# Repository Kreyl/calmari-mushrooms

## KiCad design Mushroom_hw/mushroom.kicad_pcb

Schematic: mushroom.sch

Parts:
ANT1: ANT_PCB_NOCNTR
B1, B2, B3: BAT
C1, C6, C12, C14, C19, C20, C23, C24, C26: 0.1u
C2, C8, C11, C13, C15, C16, C21, C28: 10u
C3: 10u; CAP_0603
C4, C5, C7, C29, C30, C31: 0.1u; CAP_0603
C9: 10n; CAP_0603
C10: 1u; CAP_0603
C17, C18: 10pF; CAP_0603
C22, C25, C27: 220pF
D1, D2, D3: SS14
DA1, DA3, DA4: TPS61042
DA2: NCP583SQ
DD1: STM32L151CXTX
DD2: CC2500
F1, F2, F3, F4, F5, F6, F7, F8, F9, F10, F11, F12, F13, F14, F15, F16, F17, F18, F19, F20: FUSE0R
HOLE1, HOLE2, HOLE3, HOLE4: HOLE_METALLED
L1, L2, L3: 6.8uH; IND_1210
Q1, Q3, Q6: LED_RGB_WS2812B
Q2, Q4, Q5: LED_RGB
R1, R2: 4K7; RES_0402
R3, R8, R15: 100k
R4: 150; RES_0402
R5, R11, R16: 10k; RES_0603
R6, R12, R17: 13R; RES_0603
R7, R13, R18: 120k; RES_0603
R9, R10: 390k; RES_0603
R14: 56k
R19, R20, R21: 51R; RES_0603
RP1, RP2: REFPOINT
SW1: SWITCH_H
TP1, TP2, TP3: TESTPOINT
XL1, XL5, XL6, XL8, XL9, XL10, XL12, XL13, XL14, XL16, XL17, XL18, XL20, XL21, XL22, XL24: CONN_3
XL2: ST_SWD
XL3: CONN_4
XL4: CONN_4
XL7, XL11, XL15, XL19, XL23: CONN_1
XTAL1: 27MHz; 03225

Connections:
+3.3V: C3.1, C4.1, C5.1, C7.1, C9.1, C10.1, C12.1, C13.1, C22.1, C23.1, C24.1, C25.1, C26.1, C27.1, DA2.3 (Vout), DD1.1, DD1.9, DD1.24, DD1.36, DD1.48, DD2.4 (DVDD), DD2.9 (AVDD), DD2.11 (AVDD), DD2.14 (AVDD), DD2.15 (AVDD), DD2.18 (DGUARD), XL2.1 (Vdd)
+BATT: C1.1, C2.1, C6.1, C8.1, C14.1, C15.1, C20.1, C21.1, C29.1, C30.1, C31.1, DA1.3 (Vin), DA2.1 (EN), DA2.4 (Vin), DA3.3 (Vin), DA4.3 (Vin), L1.2, L2.2, L3.2, Q1.1 (VDD), Q3.1 (VDD), Q6.1 (VDD), R9.1, SW1.2, XL6.2 (PM), XL10.2 (PM), XL14.2 (PM), XL18.2 (PM), XL22.2 (PM)
/Ant: ANT1.1, ANT1.2, DD2.12 (RF_P), DD2.13 (RF_N)
/BAT_IN: B3.A, SW1.1
/BLUE_N: DA4.1 (LED), F6.1, F10.1, F15.1, F20.2, Q5.BC (B), XL24.3
/BLUE_P: C28.1, D3.C, DA4.7 (OVP), Q2.BA, R21.2, XL5.3
/BLUE_PWM: DA4.5 (CTRL), DD1.41, R15.1, R21.1
/BRIGHTNESS: DD1.14, R7.2, R13.2, R18.2
/CC_CS: DD1.12, DD2.7 (CSn)
/CC_GDO0: DD1.13, DD2.6 (GDO0), TP2.1
/CC_GDO2: DD1.11, DD2.3 (GDO2), TP3.1
/CC_MISO: DD1.16, DD2.2 (SO(GDO1))
/CC_MOSI: DD1.17, DD2.20 (SI)
/CC_SCK: DD1.15, DD2.1 (SCLK)
/DIN0: DD1.28, Q1.4 (DIN), XL6.1
/DIN1: XL6.3, XL10.1
/DIN2: XL10.3, XL14.1
/DIN3: XL14.3, XL18.1
/DIN4: XL18.3, XL22.1
/GREEN_N: DA3.1 (LED), F5.1, F9.1, F16.1, F19.2, Q5.GC (G), XL24.2 (PM)
/GREEN_P: C16.1, D2.C, DA3.7 (OVP), Q2.GA, R20.2, XL5.2 (PM)
/GREEN_PWM: DA3.5 (CTRL), DD1.19, R8.1, R20.1
/P_SCL: DD1.45, R1.1, XL3.2 (PM)
/P_SDA: DD1.46, R2.1, XL3.4
/PeriphPwr: DD1.43, R1.2, R2.2, R4.2
/PeriphPwr1: R4.1, XL3.1
/RED_N: DA1.1 (LED), F4.1, F8.1, F17.1, F18.2, Q5.RC, XL24.1
/RED_P: C11.1, D1.C, DA1.7 (OVP), Q2.RA, R19.2, XL5.1
/RED_PWM: DA1.5 (CTRL), DD1.18, R3.1, R19.1
/SWCLK: DD1.37, XL2.2 (SWCLK)
/SWDIO: DD1.34, XL2.4 (SWDIO)
/UART_RX: DD1.31, XL1.3
/UART_TX: DD1.30, XL1.2 (PM)
GND: B1.C, C1.2, C2.2, C3.2, C4.2, C5.2, C6.2, C7.2, C8.2, C9.2, C10.2, C11.2, C12.2, C13.2, C14.2, C15.2, C16.2, C17.2, C18.2, C19.2, C20.2, C21.2, C22.2, C23.2, C24.2, C25.2, C26.2, C27.2, C28.2, C29.2, C30.2, C31.2, DA1.6 (GND), DA1.PAD (GND), DA2.2 (GND), DA3.6 (GND), DA3.PAD (GND), DA4.6 (GND), DA4.PAD (GND), DD1.8, DD1.23, DD1.35, DD1.44, DD1.47, DD2.16 (GND), DD2.19 (GND), DD2.PAD (GND), F1.1, F2.1, F3.1, F7.1, F11.1, F18.1, F19.1, F20.1, HOLE1.Hle, HOLE2.Hle, HOLE3.Hle, HOLE4.Hle, Q1.3 (GND), Q3.3 (GND), Q6.3 (GND), R3.2, R6.2, R8.2, R10.2, R12.2, R14.2, R15.2, R17.2, SW1.H, XL1.1, XL2.3 (GND), XL3.3, XL4.4, XTAL1.H
unnamed: C17.1, DD2.8 (XOSC_Q1), XTAL1.1
unnamed: C18.1, DD2.10 (XOSC_Q2), XTAL1.2
unnamed: DA1.4 (FB), R5.2, R7.1
unnamed: DA1.2 (Rs), R5.1, R6.1
unnamed: DD1.10, R9.2, R10.1
unnamed: C19.1, DD2.5 (DCOUPL)
unnamed: B1.A, B2.C
unnamed: DD2.17 (RBIAS), R14.1
unnamed: DA3.2 (Rs), R11.1, R12.1
unnamed: DA3.4 (FB), R11.2, R13.1
unnamed: D2.A, DA3.8 (SW), L2.1
unnamed: D1.A, DA1.8 (SW), L1.1
unnamed: F14.2, Q2.RC, Q4.RA
unnamed: F13.2, Q2.GC (G), Q4.GA
unnamed: XL12.3, XL13.3
unnamed: XL12.2 (PM), XL13.2 (PM)
unnamed: XL12.1, XL13.1
unnamed: XL8.3, XL9.3
unnamed: XL8.2 (PM), XL9.2 (PM)
unnamed: XL8.1, XL9.1
unnamed: F11.2, XL23.1
unnamed: F10.2, XL20.3, XL21.3
unnamed: DD1.25, XL4.3
unnamed: DD1.21, XL4.1
unnamed: DD1.22, XL4.2 (PM)
unnamed: B2.A, B3.C
unnamed: F12.2, Q2.BC (B), Q4.BA
unnamed: F14.1, F17.2, Q4.RC, Q5.RA
unnamed: F13.1, F16.2, Q4.GC (G), Q5.GA
unnamed: F12.1, F15.2, Q4.BC (B), Q5.BA
unnamed: DD1.7, TP1.1
unnamed: Q3.2 (DOUT), Q6.4 (DIN)
unnamed: Q1.2 (DOUT), Q3.4 (DIN)
unnamed: DA4.2 (Rs), R16.1, R17.1
unnamed: DA4.4 (FB), R16.2, R18.1
unnamed: D3.A, DA4.8 (SW), L3.1
unnamed: F6.2, XL16.3, XL17.3
unnamed: F9.2, XL20.2 (PM), XL21.2 (PM)
unnamed: F8.2, XL20.1, XL21.1
unnamed: F5.2, XL16.2 (PM), XL17.2 (PM)
unnamed: F4.2, XL16.1, XL17.1
unnamed: F1.2, XL7.1
unnamed: F2.2, XL11.1
unnamed: F3.2, XL15.1
unnamed: F7.2, XL19.1

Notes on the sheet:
UART
Programming
CPU
Power
Just Pins
Battery measurement
Choose capacitor max voltage carefully (30v recommended)
R=252/Iled[mA]
Place resistors and fuses if single LED is required
For WS2812B
For RGB
Solder fuses for WS2812B
Peripheral I2C Pull-Ups
Pill Connector
Pill

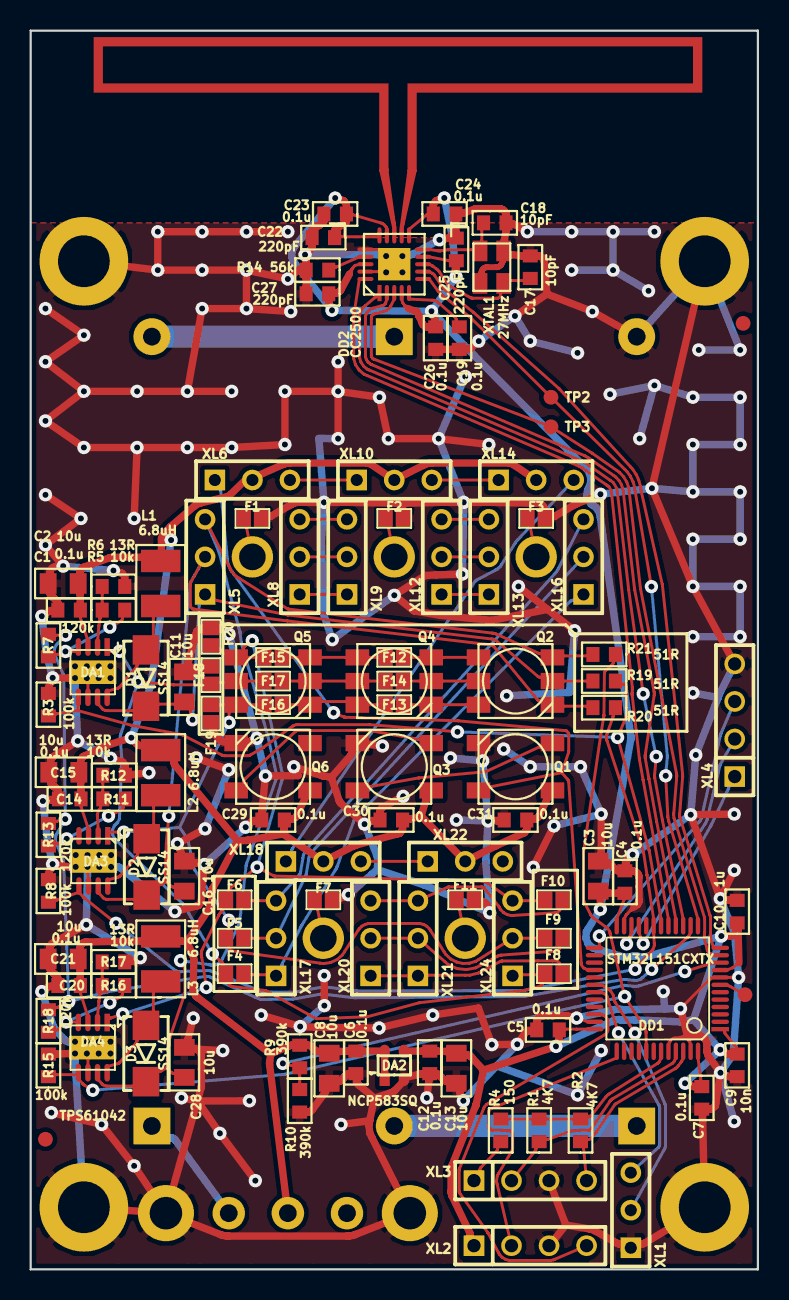
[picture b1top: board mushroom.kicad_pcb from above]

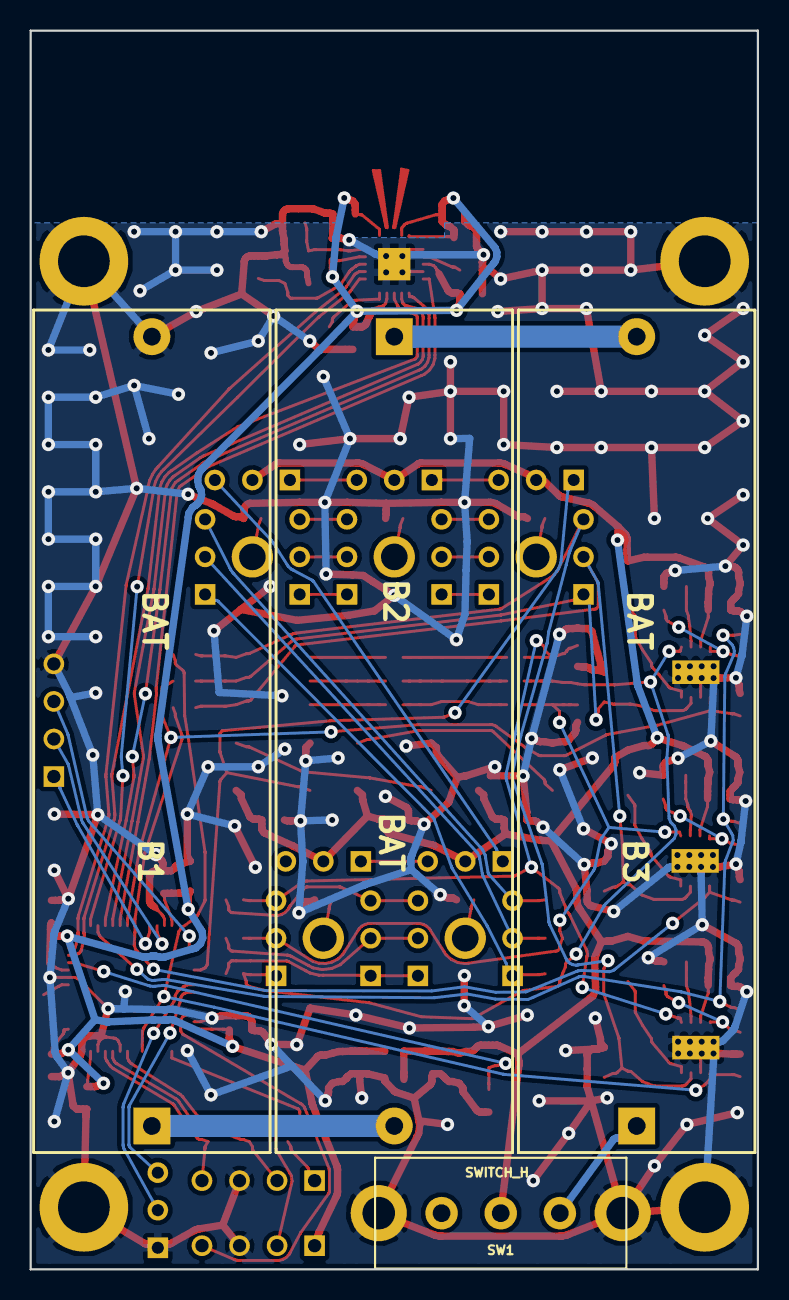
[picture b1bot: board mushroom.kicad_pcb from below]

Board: 2 copper layers, 49.2 x 83.8 mm, 129 parts (4 on the bottom side), 79 nets.

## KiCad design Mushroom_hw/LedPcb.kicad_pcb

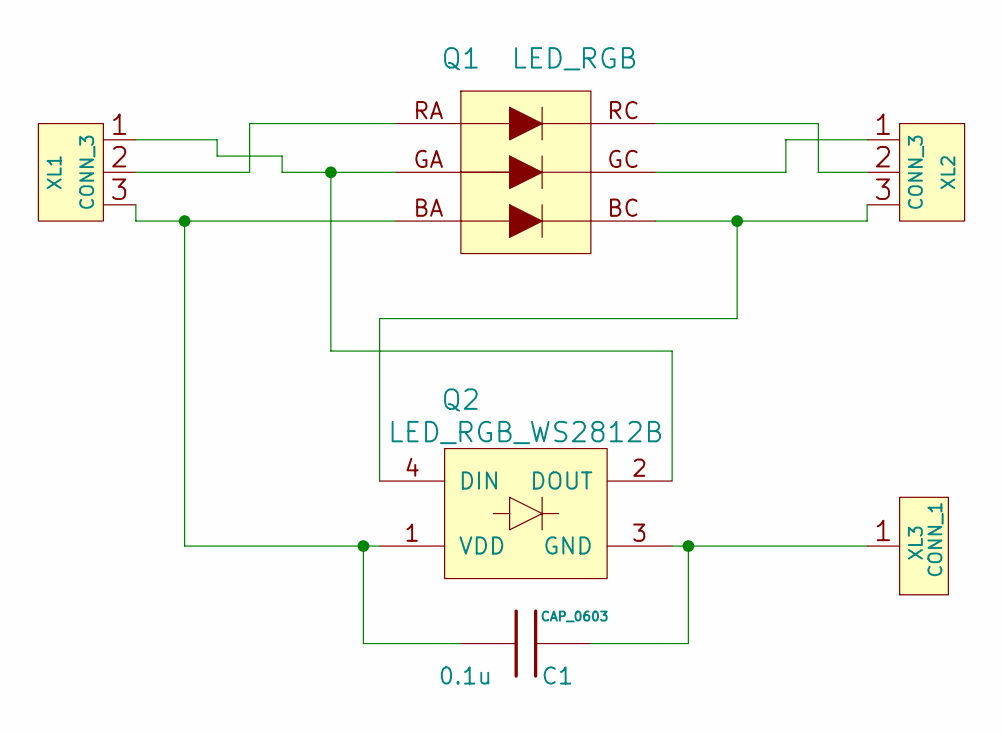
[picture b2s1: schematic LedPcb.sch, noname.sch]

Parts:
C1: 0.1u; CAP_0603
Q1: LED_RGB
Q2: LED_RGB_WS2812B
XL1, XL2: CONN_3
XL3: CONN_1

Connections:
unnamed: Q1.GA, Q2.2 (DOUT), XL1.1
unnamed: Q1.BC (B), Q2.4 (DIN), XL2.3
unnamed: Q1.RA, XL1.2 (PM)
unnamed: Q1.RC, XL2.2 (PM)
unnamed: Q1.GC (G), XL2.1
unnamed: C1.1, Q1.BA, Q2.1 (VDD), XL1.3
unnamed: C1.2, Q2.3 (GND), XL3.1

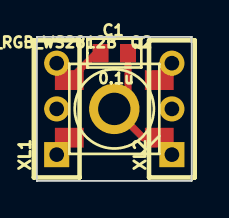
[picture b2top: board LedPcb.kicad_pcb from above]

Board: 2 copper layers, 8.6 x 8.0 mm, 6 parts (1 on the bottom side), 7 nets.

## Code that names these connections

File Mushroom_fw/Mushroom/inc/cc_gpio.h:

/*
 * cc_gpio.h
 *
 *  Created on: Nov 28, 2013
 *      Author: kreyl
 */

#ifndef CC_GPIO_H_
#define CC_GPIO_H_

// Pins
#define CC_GPIO     GPIOA
//#define CC_GDO2     1
#define CC_GDO0     3
#define CC_SCK      5
#define CC_MISO     6
#define CC_MOSI     7
#define CC_CS       2

#if CC_GDO0 == 0
#define GDO0_IRQ_HANDLER     EXTI0_IRQHandler
#elif CC_GDO0 == 1
#define GDO0_IRQ_HANDLER     EXTI1_IRQHandler
#elif CC_GDO0 == 2
#define GDO0_IRQ_HANDLER     EXTI2_IRQHandler
#elif CC_GDO0 == 3
#define GDO0_IRQ_HANDLER     EXTI3_IRQHandler
#elif CC_GDO0 == 4
#define GDO0_IRQ_HANDLER     EXTI4_IRQHandler
#endif

// SPI
#define CC_SPI      SPI1

#endif /* CC_GPIO_H_ */

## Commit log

2014-04-12 + everything
2014-04-15 proceeding
2014-04-20 Receives and sets color + AppID
2014-04-20 Dir change
2014-04-20 + Candle project * Mushrooms edited and tested to work in new dirs
2014-04-21 + keys.h: every key now has its own timecounter
2014-04-21 + Sleep timer + Color '!=' operator
2014-04-21 Backup Registers color storage, not working yet
2014-04-21 + Color saved in BackupRegister and loaded at start
2014-04-21 + Sleep mode implemented Release candidate
2014-04-21 * Mushroom edited to be compliant with candle
2014-04-24 + Charging indication
2014-04-24 Mushroom: sleep work started
2014-04-25 + OnSmoothStart/End functions added - Sleep modes disabled for mushroom
2015-03-29 Migrating wiki contents from Google Code
